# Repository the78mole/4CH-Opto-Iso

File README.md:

# 4CH-Opto-Iso

A 4 Channel Opto Isolator

The schematic can be found [here](doc/4CH-Opto-ISO.pdf).

To access the bom, use this link: https://htmlpreview.github.io/?https://github.com/the78mole/4CH-Opto-Iso/blob/main/bom/ibom.html

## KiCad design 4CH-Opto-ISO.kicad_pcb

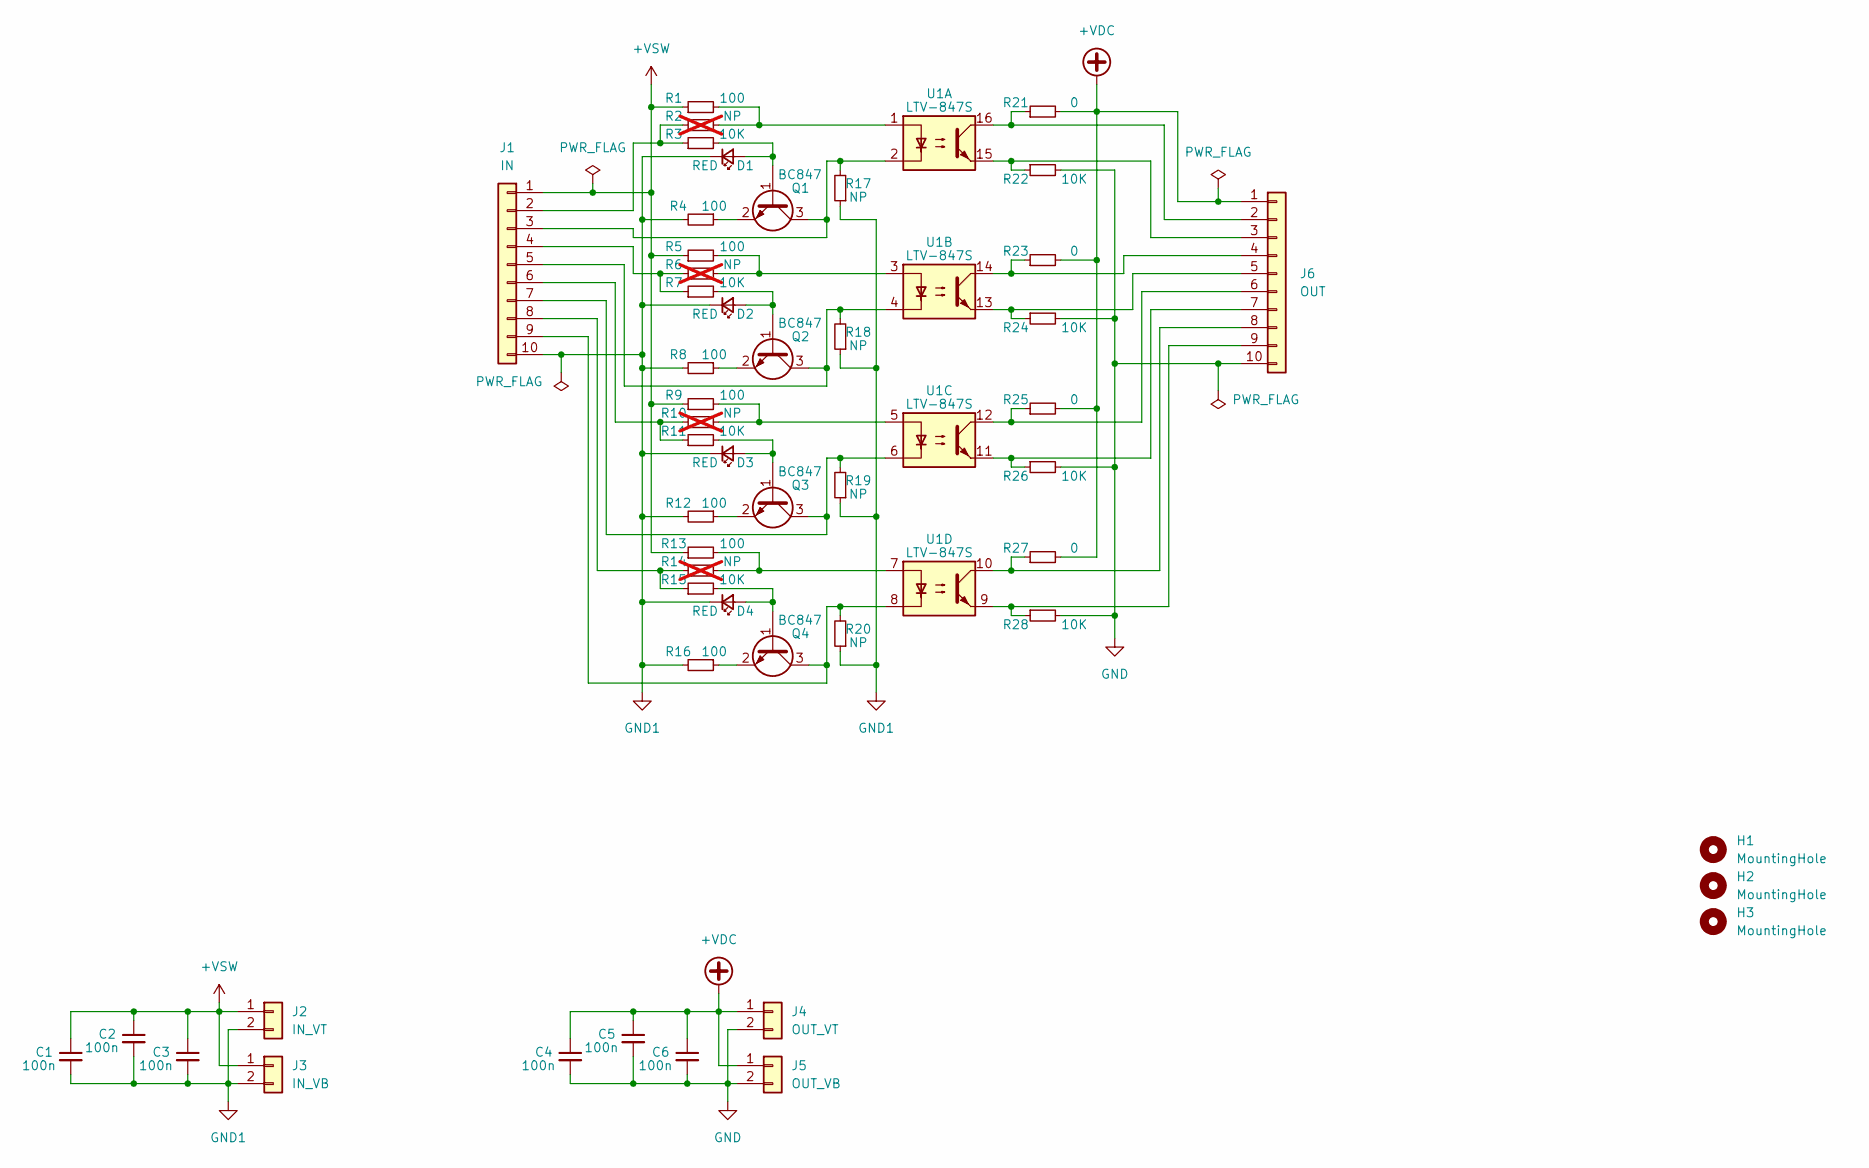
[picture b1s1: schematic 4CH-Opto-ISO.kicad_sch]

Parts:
C1, C2, C3, C4, C5, C6: 100n; C_0603_1608Metric_Pad1.08x0.95mm_HandSolder
D1, D2, D3, D4: RED; LED_0603_1608Metric_Pad1.05x0.95mm_HandSolder
H1, H2, H3: MountingHole; MountingHole_3.2mm_M3_DIN965
J1: IN; PinSocket_1x10_P2.54mm_Horizontal
J2: IN_VT; PinSocket_1x02_P2.54mm_Horizontal
J3: IN_VB; PinHeader_1x02_P2.54mm_Horizontal
J4: OUT_VT; PinSocket_1x02_P2.54mm_Horizontal
J5: OUT_VB; PinHeader_1x02_P2.54mm_Horizontal
J6: OUT; PinHeader_1x10_P2.54mm_Horizontal
Q1, Q2, Q3, Q4: BC847; SOT-23
R1, R4, R5, R8, R9, R12, R13, R16: 100; R_0603_1608Metric_Pad0.98x0.95mm_HandSolder
R2, R6, R10, R14: NP; R_0603_1608Metric_Pad0.98x0.95mm_HandSolder; not fitted
R3, R7, R11, R15, R22, R24, R26, R28: 10K; R_0603_1608Metric_Pad0.98x0.95mm_HandSolder
R17, R18, R19, R20: NP; R_0603_1608Metric_Pad0.98x0.95mm_HandSolder
R21, R23, R25, R27: 0; R_0603_1608Metric_Pad0.98x0.95mm_HandSolder
U1: LTV-847S; SMDIP-16_W9.53mm

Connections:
+VDC: C4.1, C5.1, C6.1, J4.1, J5.1, J6.1, R21.2, R23.2, R25.2, R27.2
+VSW: C1.1, C2.1, C3.1, J1.1, J2.1, J3.1, R1.1, R5.1, R9.1, R13.1
GND: C4.2, C5.2, C6.2, J4.2, J5.2, J6.10, R22.2, R24.2, R26.2, R28.2
GND1: C1.2, C2.2, C3.2, D1.1 (K), D2.1 (K), D3.1 (K), D4.1 (K), J1.10, J2.2, J3.2, R4.2, R8.2, R12.2, R16.2, R17.1, R18.1, R19.1, R20.1
unnamed: D1.2 (A), Q1.1 (B), R3.2
unnamed: D2.2 (A), Q2.1 (B), R7.2
unnamed: D3.2 (A), Q3.1 (B), R11.2
unnamed: D4.2 (A), Q4.1 (B), R15.2
unnamed: J1.2, R2.1, R3.1
unnamed: J1.3, Q1.3 (C), R17.2, U1.2
unnamed: J1.4, R6.1, R7.1
unnamed: J1.5, Q2.3 (C), R18.2, U1.4
unnamed: J1.6, R10.1, R11.1
unnamed: J1.7, Q3.3 (C), R19.2, U1.6
unnamed: J1.8, R14.1, R15.1
unnamed: J1.9, Q4.3 (C), R20.2, U1.8
unnamed: J6.2, R21.1, U1.16
unnamed: J6.3, R22.1, U1.15
unnamed: J6.4, R23.1, U1.14
unnamed: J6.5, R24.1, U1.13
unnamed: J6.6, R25.1, U1.12
unnamed: J6.7, R26.1, U1.11
unnamed: J6.8, R27.1, U1.10
unnamed: J6.9, R28.1, U1.9
unnamed: Q1.2 (E), R4.1
unnamed: Q2.2 (E), R8.1
unnamed: Q3.2 (E), R12.1
unnamed: Q4.2 (E), R16.1
unnamed: R1.2, R2.2, U1.1
unnamed: R5.2, R6.2, U1.3
unnamed: R9.2, R10.2, U1.5
unnamed: R13.2, R14.2, U1.7

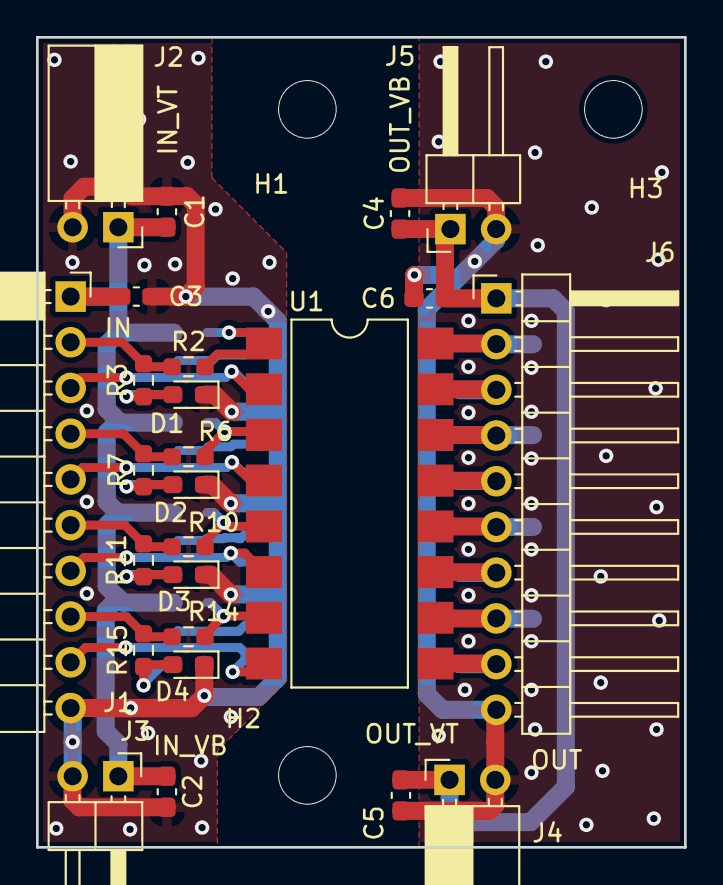
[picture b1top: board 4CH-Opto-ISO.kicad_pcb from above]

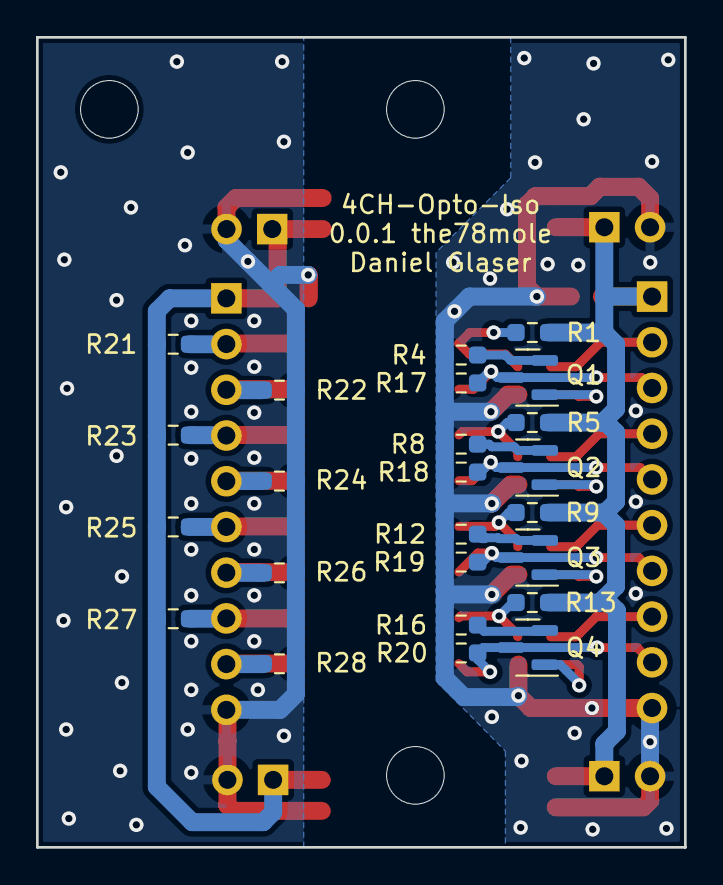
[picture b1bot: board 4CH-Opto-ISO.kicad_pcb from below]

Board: 2 copper layers, 36.0 x 45.0 mm, 52 parts (24 on the bottom side), 32 nets.

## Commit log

2023-09-26 Initial commit revision 0.0.1
2023-09-26 Migration to KiCad 7.0
